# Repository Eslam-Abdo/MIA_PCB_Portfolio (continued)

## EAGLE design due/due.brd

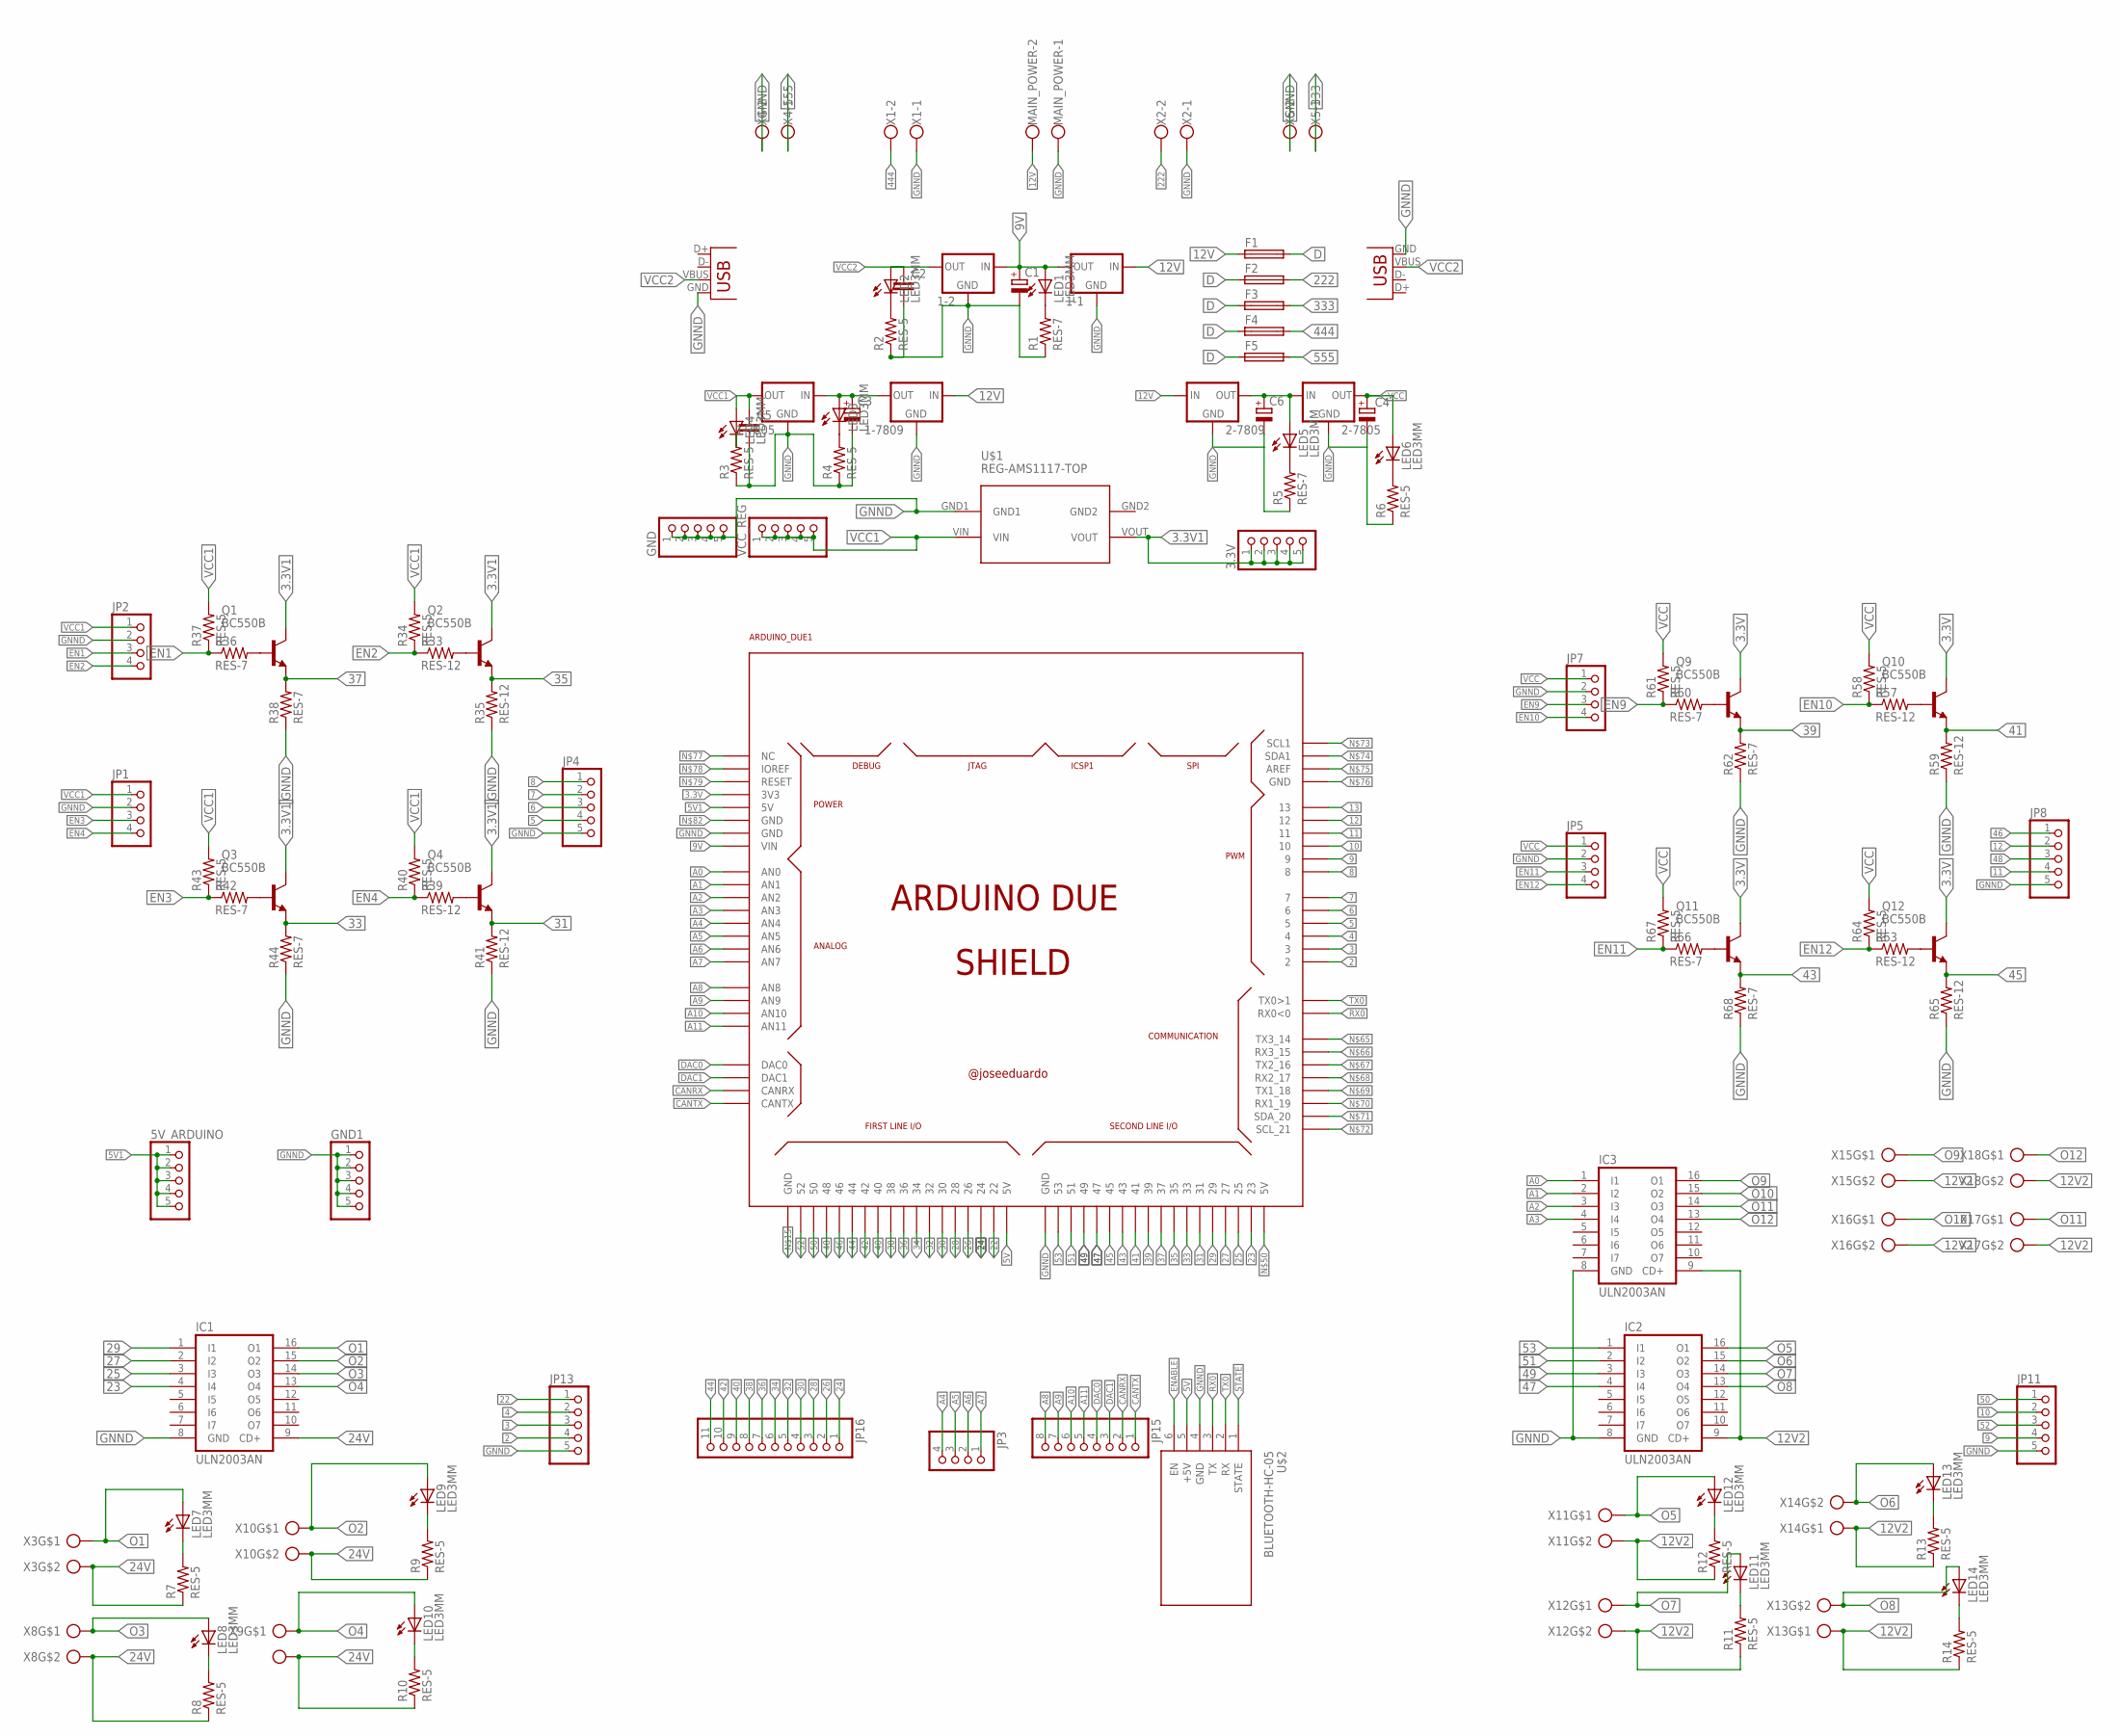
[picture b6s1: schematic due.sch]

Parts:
1-1, 1-2, 1-7805, 1-7809, 2-7805, 2-7809: 78XXS
3.3V, 5V_ARDUINO: PINHD-1X5; 1X05
ARDUINO_DUE1: ARDUINO_DUE_SHIELD
C1, C3, C4, C6: CAP_POL; E3,5-8
C2, C5: CAPACITOR; C025-025X050
F1, F2, F3, F4, F5: FUSE_HOLDER; SH22,5A
GND, GND1: PINHD-1X5; 1X05
IC1, IC2, IC3: ULN2003AN; DIL16
JP1, JP2, JP3, JP5, JP7: PINHD-1X4; 1X04
JP4, JP8, JP11, JP13: PINHD-1X5; 1X05
JP15: PINHD-1X8; 1X08
JP16: PINHD-1X11; 1X11
LED1, LED2, LED3, LED4, LED5, LED6, LED7, LED8, LED9, LED10, LED11, LED12, LED13, LED14: LED3MM
MAIN_POWER: ROSTA.POWER; W239-302
Q1, Q2, Q3, Q4, Q9, Q10, Q11, Q12: BC550B; TO92-EBC
R1, R5, R36, R38, R42, R44, R60, R62, R66, R68: RES-7; 0204/7
R2, R3, R4, R6, R7, R8, R9, R10, R11, R12, R13, R14, R34, R37, R40, R43, R58, R61, R64, R67: RES-5; 0204/5
R33, R35, R39, R41, R57, R59, R63, R65: RES-12; 0207/12
U$1: REG-AMS1117-TOP; REG-AMS1117_TOP
U$2: BLUETOOTH-HC-05; WIRELESS-BLUETOOTH-HC-05
VCC_REG: PINHD-1X5; 1X05
X1, X2, X4, X5: ROSTA.POWER; W239-302
X3, X8, X9, X10, X11, X12, X13, X14, X15, X16, X17, X18: CON_PTR_2; AK300/2
X6, X7: USB-A-H

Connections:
2: ARDUINO_DUE1.2, JP13.4
3: ARDUINO_DUE1.3, JP13.3
3.3V: ARDUINO_DUE1.3V3, Q9.C, Q10.C, Q11.C, Q12.C
3.3V1: 3.3V.1, 3.3V.2, 3.3V.3, 3.3V.4, 3.3V.5, Q1.C, Q2.C, Q3.C, Q4.C, U$1.VOUT
4: ARDUINO_DUE1.4, JP13.2
5: ARDUINO_DUE1.5, JP4.4
5V: ARDUINO_DUE1.5V0_1 (5V), U$2.5 (+5V)
5V1: 5V_ARDUINO.1, 5V_ARDUINO.2, 5V_ARDUINO.3, 5V_ARDUINO.4, 5V_ARDUINO.5, ARDUINO_DUE1.5V0 (5V)
6: ARDUINO_DUE1.6, JP4.3
7: ARDUINO_DUE1.7, JP4.2
8: ARDUINO_DUE1.8, JP4.1
9: ARDUINO_DUE1.9, JP11.4
9V: 1-1.OUT, 1-2.IN, ARDUINO_DUE1.VIN, C1.+, LED1.A
10: ARDUINO_DUE1.10, JP11.2
11: ARDUINO_DUE1.11, JP8.4
12: ARDUINO_DUE1.12, JP8.2
12V: 1-1.IN, 1-7809.IN, 2-7809.IN, F1.1, MAIN_POWER.2
12V2: IC2.9 (CD+), IC3.9 (CD+), R11.1, R12.1, R13.1, R14.1, X11.2, X12.2, X13.1, X14.1, X15.2, X16.2, X17.2, X18.2
13: ARDUINO_DUE1.13
22: ARDUINO_DUE1.22, JP13.1
23: ARDUINO_DUE1.23, IC1.4 (I4)
24: ARDUINO_DUE1.24, JP16.1
24V: IC1.9 (CD+), R7.1, R8.1, R9.1, R10.1, X3.2, X8.2, X9.2, X10.2
25: ARDUINO_DUE1.25, IC1.3 (I3)
26: ARDUINO_DUE1.26, JP16.2
27: ARDUINO_DUE1.27, IC1.2 (I2)
28: ARDUINO_DUE1.28, JP16.3
29: ARDUINO_DUE1.29, IC1.1 (I1)
30: ARDUINO_DUE1.30, JP16.4
31: ARDUINO_DUE1.31, Q4.E, R41.2
32: ARDUINO_DUE1.32, JP16.5
33: ARDUINO_DUE1.33, Q3.E, R44.2
34: ARDUINO_DUE1.34, JP16.6
35: ARDUINO_DUE1.35, Q2.E, R35.2
36: ARDUINO_DUE1.36, JP16.7
37: ARDUINO_DUE1.37, Q1.E, R38.2
38: ARDUINO_DUE1.38, JP16.8
39: ARDUINO_DUE1.39, Q9.E, R62.2
40: ARDUINO_DUE1.40, JP16.9
41: ARDUINO_DUE1.41, Q10.E, R59.2
42: ARDUINO_DUE1.42, JP16.10
43: ARDUINO_DUE1.43, Q11.E, R68.2
44: ARDUINO_DUE1.44, JP16.11
45: ARDUINO_DUE1.45, Q12.E, R65.2
46: ARDUINO_DUE1.46, JP8.1
47: ARDUINO_DUE1.47, IC2.4 (I4)
48: ARDUINO_DUE1.48, JP8.3
49: ARDUINO_DUE1.49, IC2.3 (I3)
50: ARDUINO_DUE1.50, JP11.1
51: ARDUINO_DUE1.51, IC2.2 (I2)
52: ARDUINO_DUE1.52, JP11.3
53: ARDUINO_DUE1.53, IC2.1 (I1)
222: F2.2, X2.2
333: F3.2, X5.1
444: F4.2, X1.2
555: F5.2, X4.1
A0: ARDUINO_DUE1.A0 (AN0), IC3.1 (I1)
A1: ARDUINO_DUE1.A1 (AN1), IC3.2 (I2)
A2: ARDUINO_DUE1.A2 (AN2), IC3.3 (I3)
A3: ARDUINO_DUE1.A3 (AN3), IC3.4 (I4)
A4: ARDUINO_DUE1.A4 (AN4), JP3.4
A5: ARDUINO_DUE1.A5 (AN5), JP3.3
A6: ARDUINO_DUE1.A6 (AN6), JP3.2
A7: ARDUINO_DUE1.A7 (AN7), JP3.1
A8: ARDUINO_DUE1.A8 (AN8), JP15.8
A9: ARDUINO_DUE1.A9 (AN9), JP15.7
A10: ARDUINO_DUE1.A10 (AN10), JP15.6
A11: ARDUINO_DUE1.A11 (AN11), JP15.5
CANRX: ARDUINO_DUE1.CANRX, JP15.2
CANTX: ARDUINO_DUE1.CANTX, JP15.1
D: F1.2, F2.1, F3.1, F4.1, F5.1
DAC0: ARDUINO_DUE1.DAC0, JP15.4
DAC1: ARDUINO_DUE1.DAC1, JP15.3
EN1: JP2.3, R36.1, R37.1
EN2: JP2.4, R33.1, R34.1
EN3: JP1.3, R42.1, R43.1
EN4: JP1.4, R39.1, R40.1
EN9: JP7.3, R60.1, R61.1
EN10: JP7.4, R57.1, R58.1
EN11: JP5.3, R66.1, R67.1
EN12: JP5.4, R63.1, R64.1
ENABLE: U$2.6 (EN)
GNND: 1-1.GND, 1-2.GND, 1-7805.GND, 1-7809.GND, 2-7805.GND, 2-7809.GND, ARDUINO_DUE1.GND_1 (GND), ARDUINO_DUE1.GND_3 (GND), C1.-, C2.2, C3.-, C4.-, C5.2, C6.-, GND.1, GND.2, GND.3, GND.4, GND.5, GND1.1, GND1.2, GND1.3, GND1.4, GND1.5, IC1.8 (GND), IC2.8 (GND), IC3.8 (GND), JP1.2, JP2.2, JP4.5, JP5.2, JP7.2, JP8.5, JP11.5, JP13.5, MAIN_POWER.1, R1.1, R2.1, R3.1, R4.1, R5.1, R6.1, R35.1, R38.1, R41.1, R44.1, R59.1, R62.1, R65.1, R68.1, U$1.GND1, U$2.4 (GND), X1.1, X2.1, X4.2, X5.2, X6.GND, X7.GND
unnamed: LED12.K (C), R12.2
unnamed: LED1.K (C), R1.2
unnamed: C2.1, LED2.A
unnamed: LED4.K (C), R3.2
unnamed: LED3.K (C), R4.2
unnamed: 2-7805.IN, 2-7809.OUT, C6.+, LED5.A
unnamed: LED2.K (C), R2.2
unnamed: LED5.K (C), R5.2
unnamed: LED6.K (C), R6.2
unnamed: LED11.K (C), R11.2
unnamed: LED13.K (C), R13.2
unnamed: LED14.K (C), R14.2
unnamed: LED10.K (C), R10.2
unnamed: LED9.K (C), R9.2
unnamed: 1-7805.IN, 1-7809.OUT, C3.+, LED3.A
unnamed: LED8.K (C), R8.2
unnamed: LED7.K (C), R7.2
unnamed: Q2.B, R33.2
unnamed: Q1.B, R36.2
unnamed: Q4.B, R39.2
unnamed: Q3.B, R42.2
unnamed: Q10.B, R57.2
unnamed: Q9.B, R60.2
unnamed: Q12.B, R63.2
unnamed: Q11.B, R66.2
O1: IC1.16 (O1), LED7.A, X3.1
O2: IC1.15 (O2), LED9.A, X10.1
O3: IC1.14 (O3), LED8.A, X8.1
O4: IC1.13 (O4), LED10.A, X9.1
O5: IC2.16 (O1), LED12.A, X11.1
O6: IC2.15 (O2), LED13.A, X14.2
O7: IC2.14 (O3), LED11.A, X12.1
O8: IC2.13 (O4), LED14.A, X13.2
O9: IC3.16 (O1), X15.1
O10: IC3.15 (O2), X16.1
O11: IC3.14 (O3), X17.1
O12: IC3.13 (O4), X18.1
RX0: ARDUINO_DUE1.0 (RX0<0), U$2.3 (TX)
STATE: U$2.1 (STATE)
TX0: ARDUINO_DUE1.1 (TX0>1), U$2.2 (RX)
VCC: 2-7805.OUT, C4.+, JP5.1, JP7.1, LED6.A, R58.2, R61.2, R64.2, R67.2
VCC1: 1-7805.OUT, C5.1, JP1.1, JP2.1, LED4.A, R34.2, R37.2, R40.2, R43.2, U$1.VIN, VCC_REG.1, VCC_REG.2, VCC_REG.3, VCC_REG.4, VCC_REG.5
VCC2: 1-2.OUT, X6.VBUS, X7.VBUS

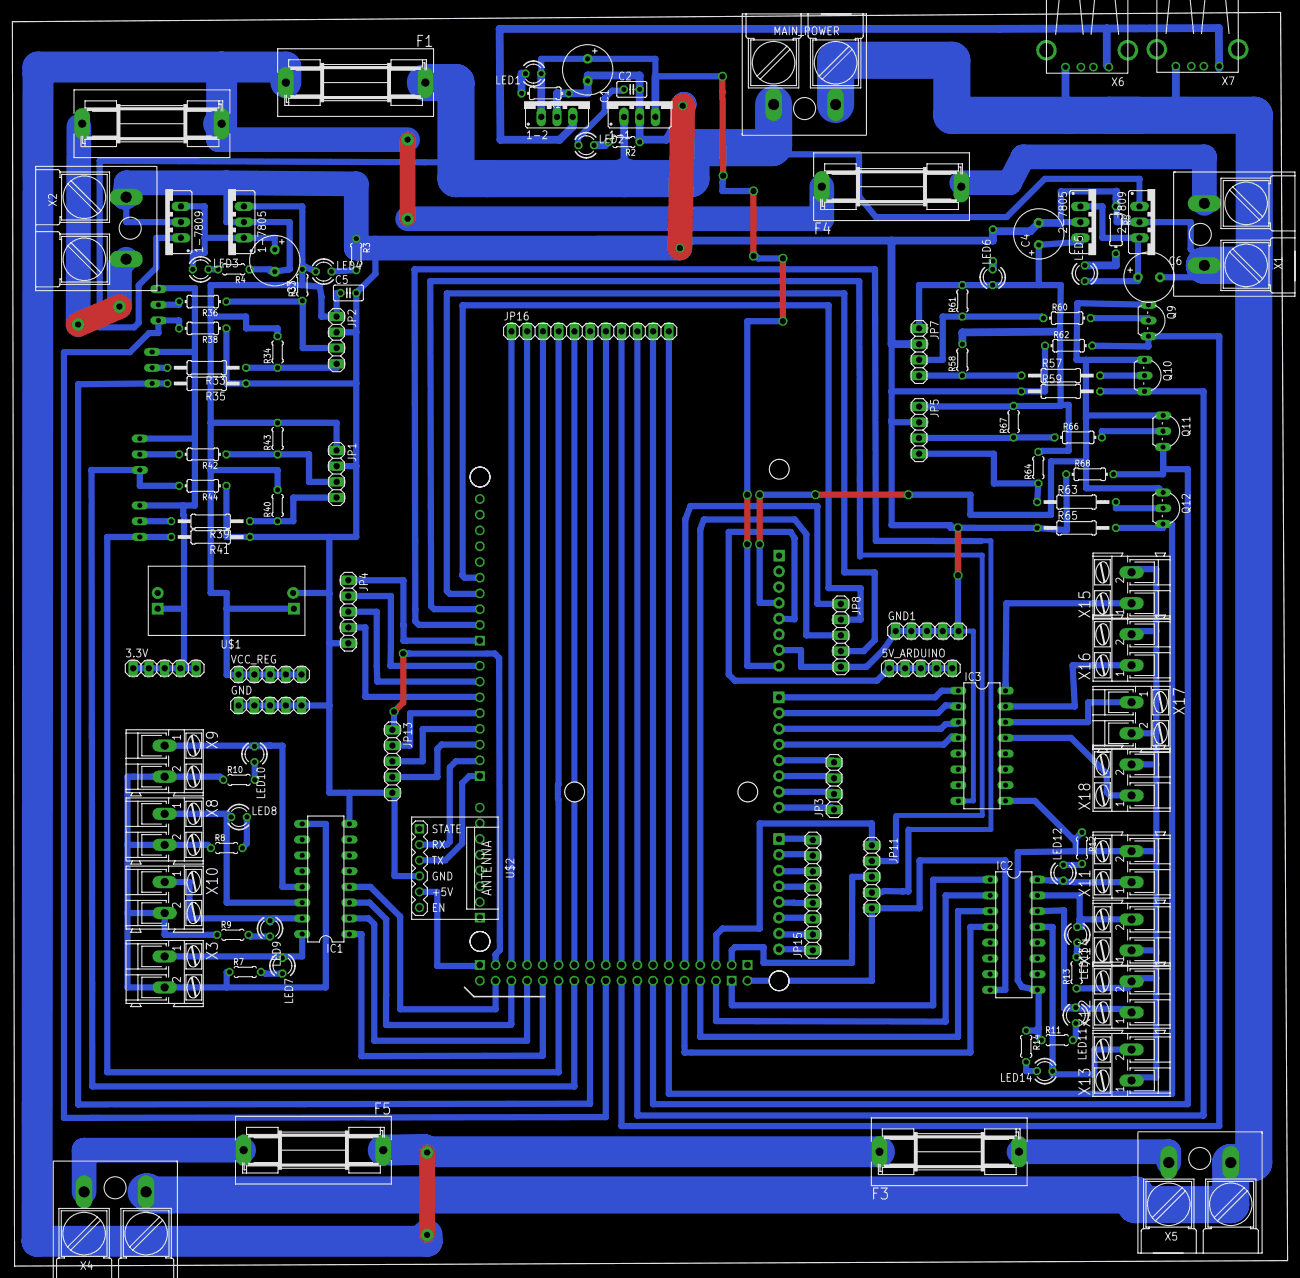
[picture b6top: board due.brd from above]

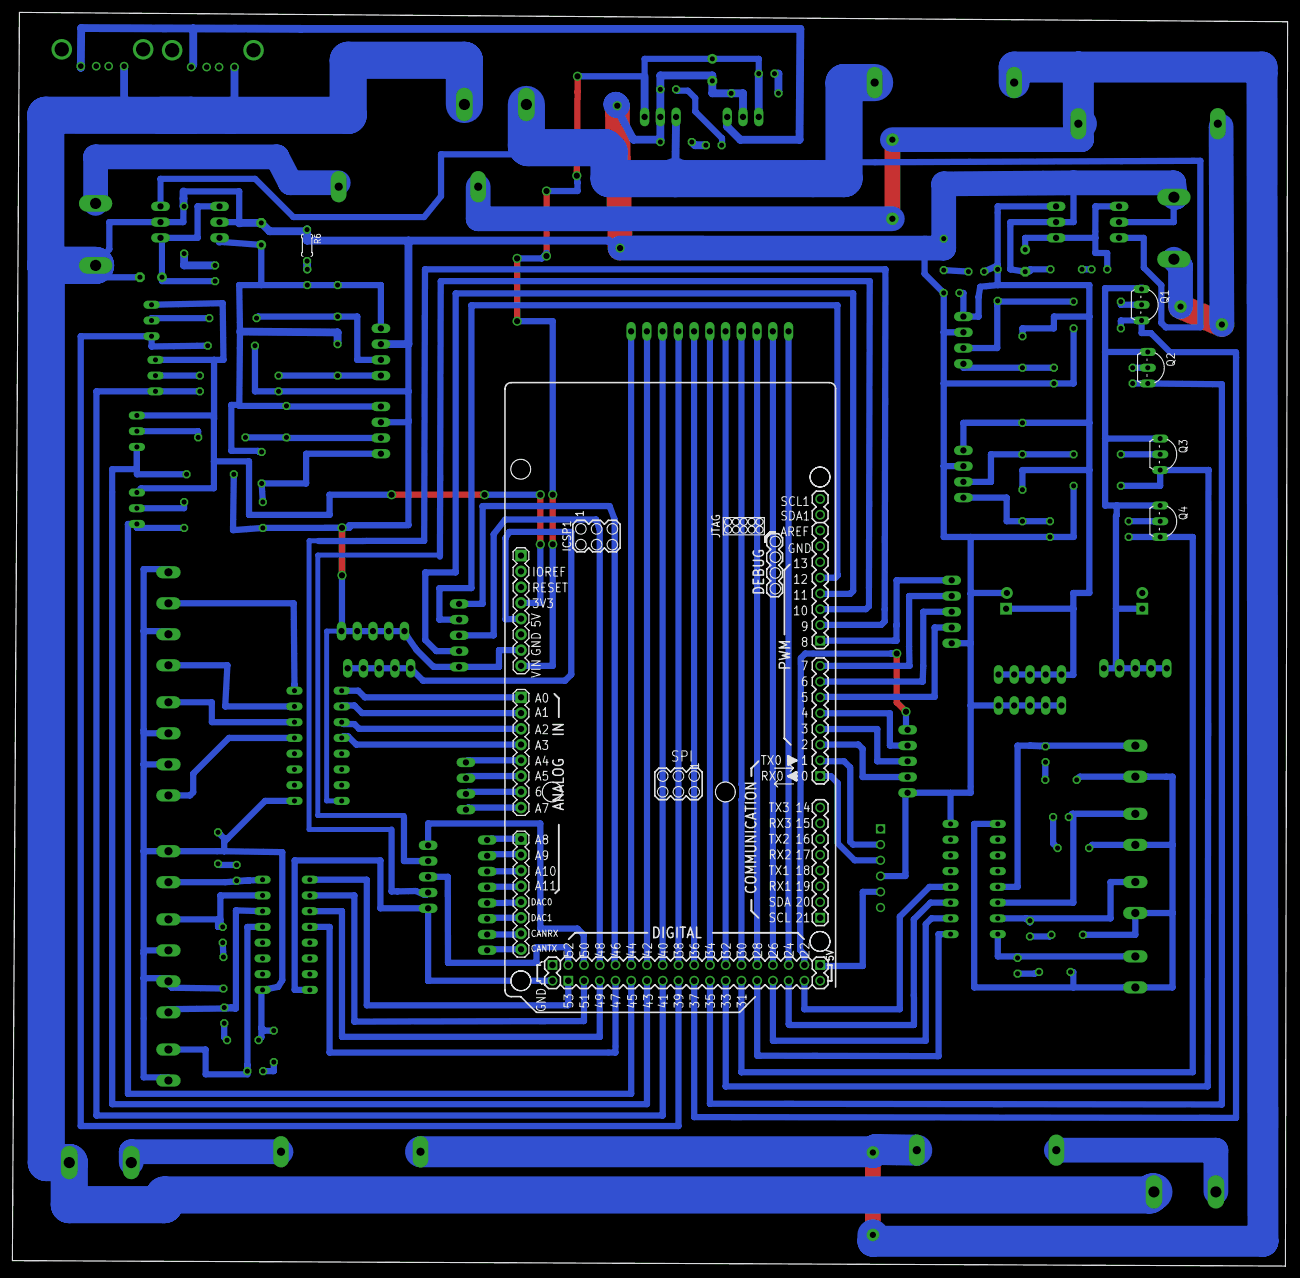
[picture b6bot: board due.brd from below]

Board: 2 copper layers, 205.7 x 202.3 mm, 118 parts (6 on the bottom side), 123 nets.

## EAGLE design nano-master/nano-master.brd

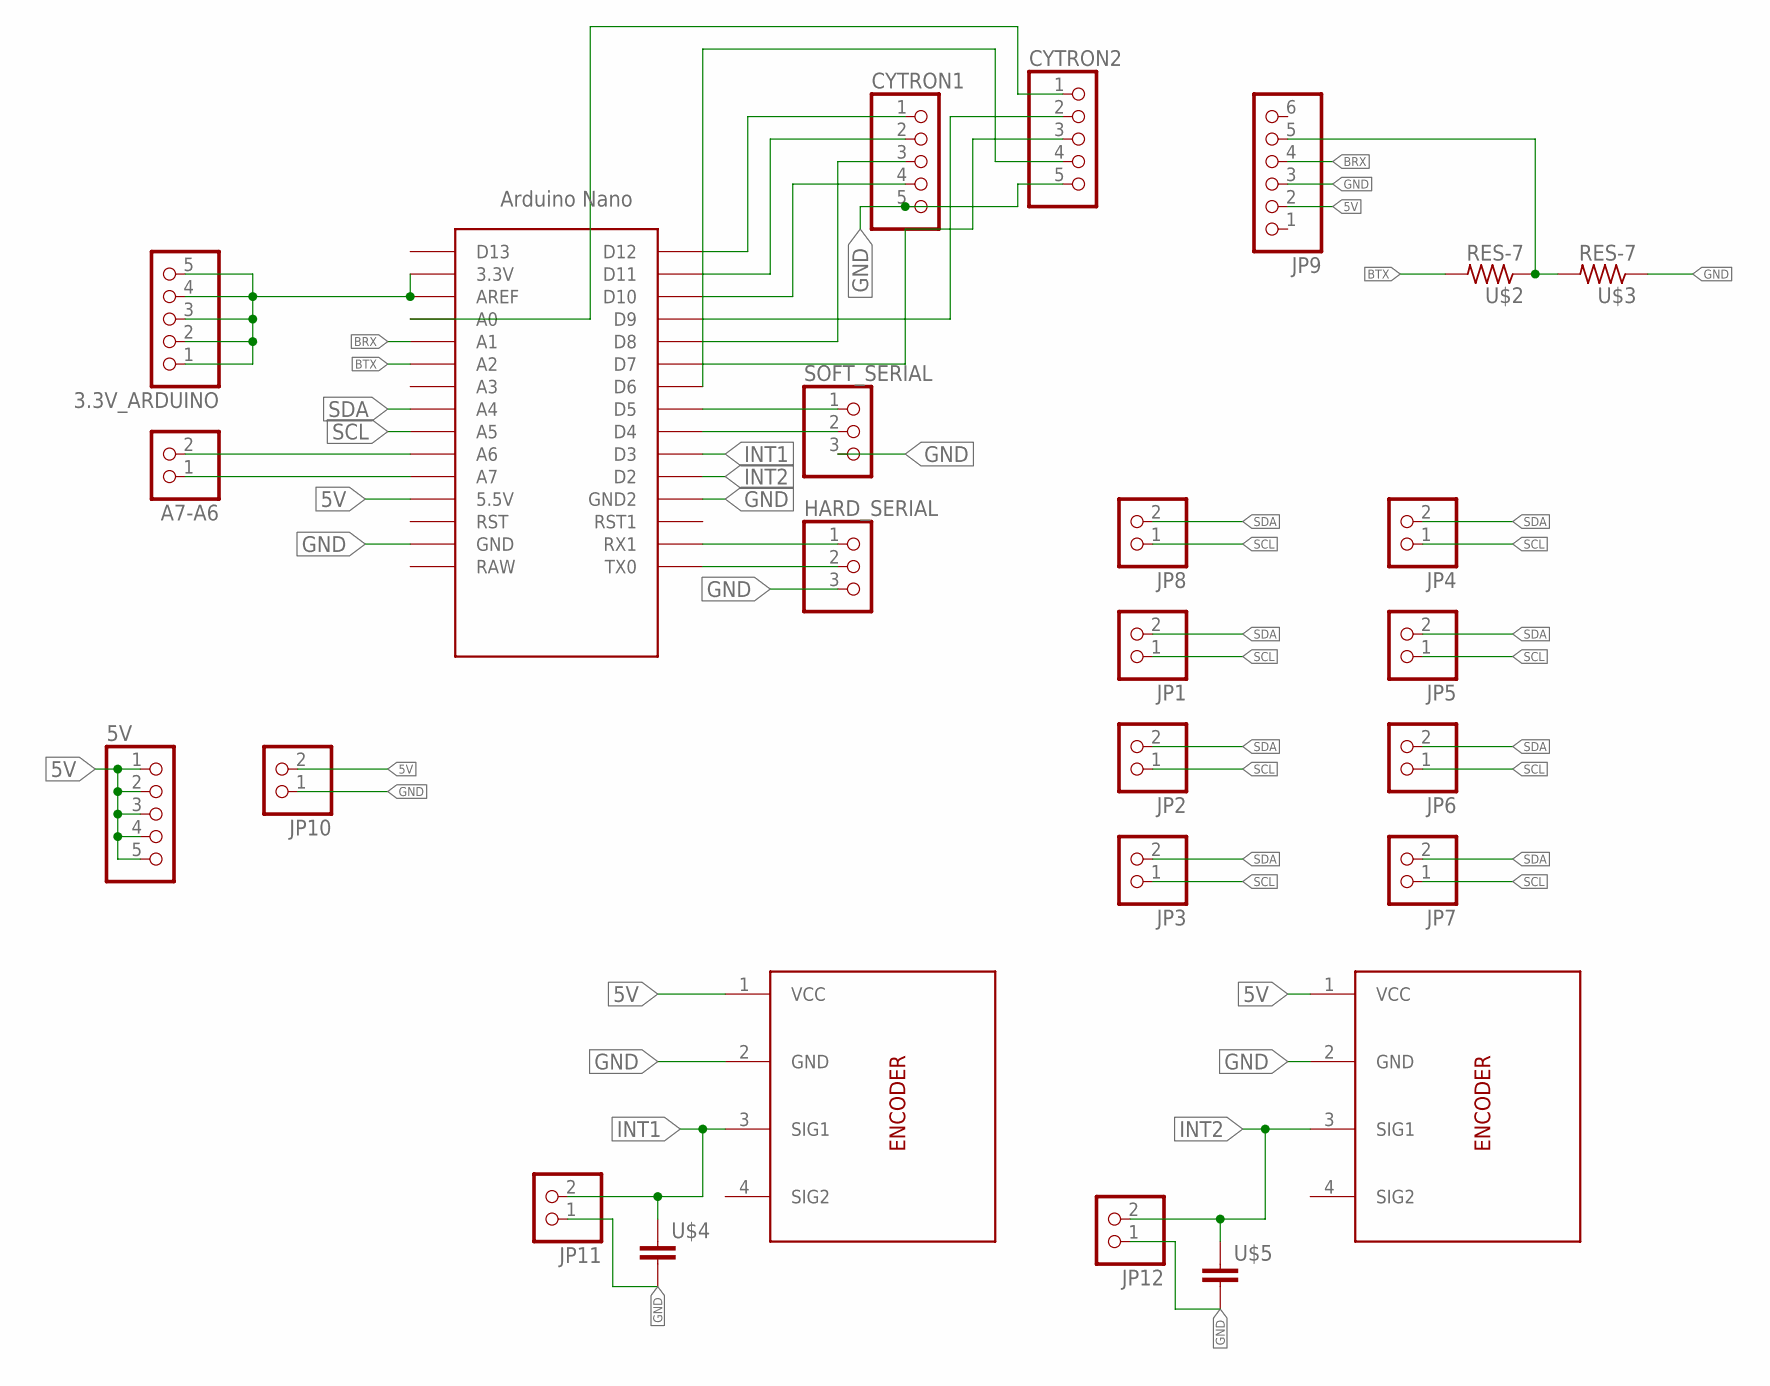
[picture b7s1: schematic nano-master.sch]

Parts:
3.3V_ARDUINO, 5V: PINHD-1X5; 1X05
A7-A6: PINHD-1X2; 1X02
CYTRON1, CYTRON2: PINHD-1X5; 1X05
ENCODER1, ENCODER2: ENCODER; 1X04_DATA
HARD_SERIAL: PINHD-1X3; 1X03
JP1, JP2, JP3, JP4, JP5, JP6, JP7, JP8, JP10, JP11, JP12: PINHD-1X2; 1X02
JP9: PINHD-1X6; 1X06
SOFT_SERIAL: PINHD-1X3; 1X03
U$1: ARDUINO_NANO; NANO
U$2, U$3: RES-7; 0204/7
U$4, U$5: CAPACITOR; C025-025X050

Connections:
5V: 5V.1, 5V.2, 5V.3, 5V.4, 5V.5, ENCODER1.1 (VCC), ENCODER2.1 (VCC), JP9.2, JP10.2, U$1.5V (5.5V)
BRX: JP9.4, U$1.A1
BTX: U$1.A2, U$2.2
GND: CYTRON1.5, CYTRON2.5, ENCODER1.2 (GND), ENCODER2.2 (GND), HARD_SERIAL.3, JP9.3, JP10.1, JP11.1, JP12.1, SOFT_SERIAL.3, U$1.GND, U$1.GND1 (GND2), U$3.1, U$4.2, U$5.2
INT1: ENCODER2.3 (SIG1), JP11.2, U$1.D3, U$4.1
INT2: ENCODER1.3 (SIG1), JP12.2, U$1.D2, U$5.1
unnamed: SOFT_SERIAL.1, U$1.D5
unnamed: SOFT_SERIAL.2, U$1.D4
unnamed: HARD_SERIAL.1, U$1.RX1
unnamed: HARD_SERIAL.2, U$1.TX0
unnamed: CYTRON1.1, U$1.D12
unnamed: CYTRON1.2, U$1.D11
unnamed: CYTRON1.4, U$1.D10
unnamed: CYTRON2.2, U$1.D9
unnamed: CYTRON1.3, U$1.D8
unnamed: CYTRON2.3, U$1.D7
unnamed: CYTRON2.4, U$1.D6
unnamed: CYTRON2.1, U$1.A0
unnamed: JP9.5, U$2.1, U$3.2
unnamed: A7-A6.1, U$1.A7
unnamed: A7-A6.2, U$1.A6
unnamed: 3.3V_ARDUINO.1, 3.3V_ARDUINO.2, 3.3V_ARDUINO.3, 3.3V_ARDUINO.4, 3.3V_ARDUINO.5, U$1.3.3V, U$1.AREF
SCL: JP1.1, JP2.1, JP3.1, JP4.1, JP5.1, JP6.1, JP7.1, JP8.1, U$1.A5
SDA: JP1.2, JP2.2, JP3.2, JP4.2, JP5.2, JP6.2, JP7.2, JP8.2, U$1.A4

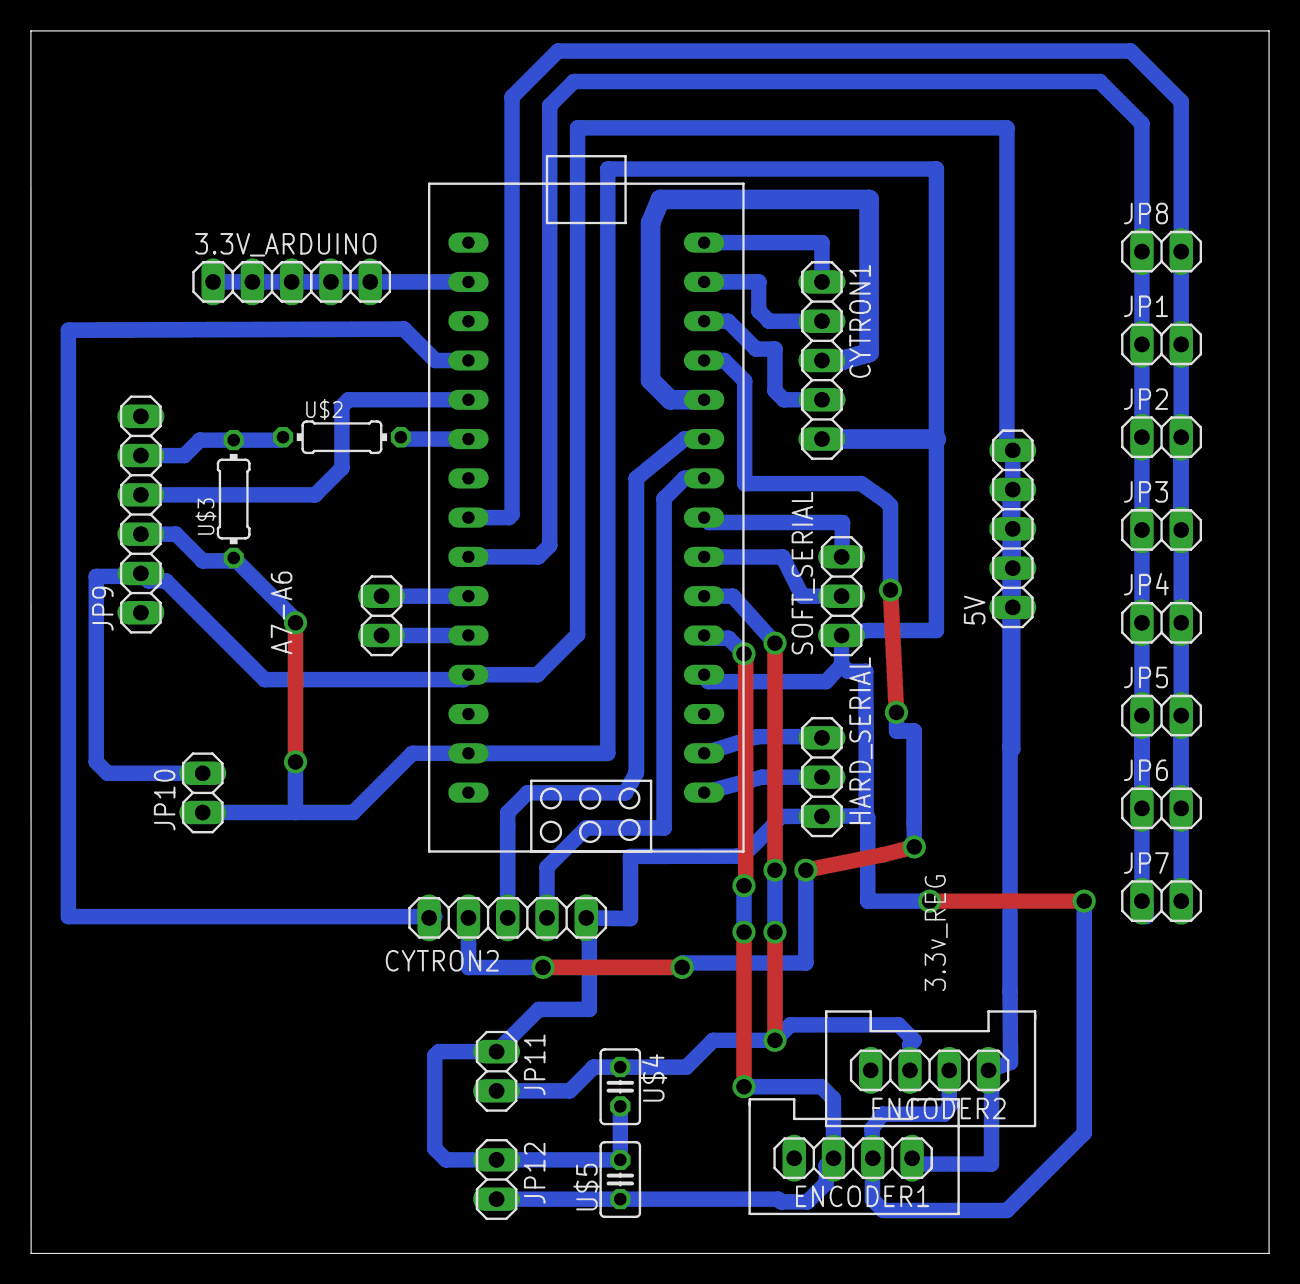
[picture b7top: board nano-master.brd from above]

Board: 2 copper layers, 80.1 x 79.1 mm, 26 parts (0 on the bottom side), 24 nets.

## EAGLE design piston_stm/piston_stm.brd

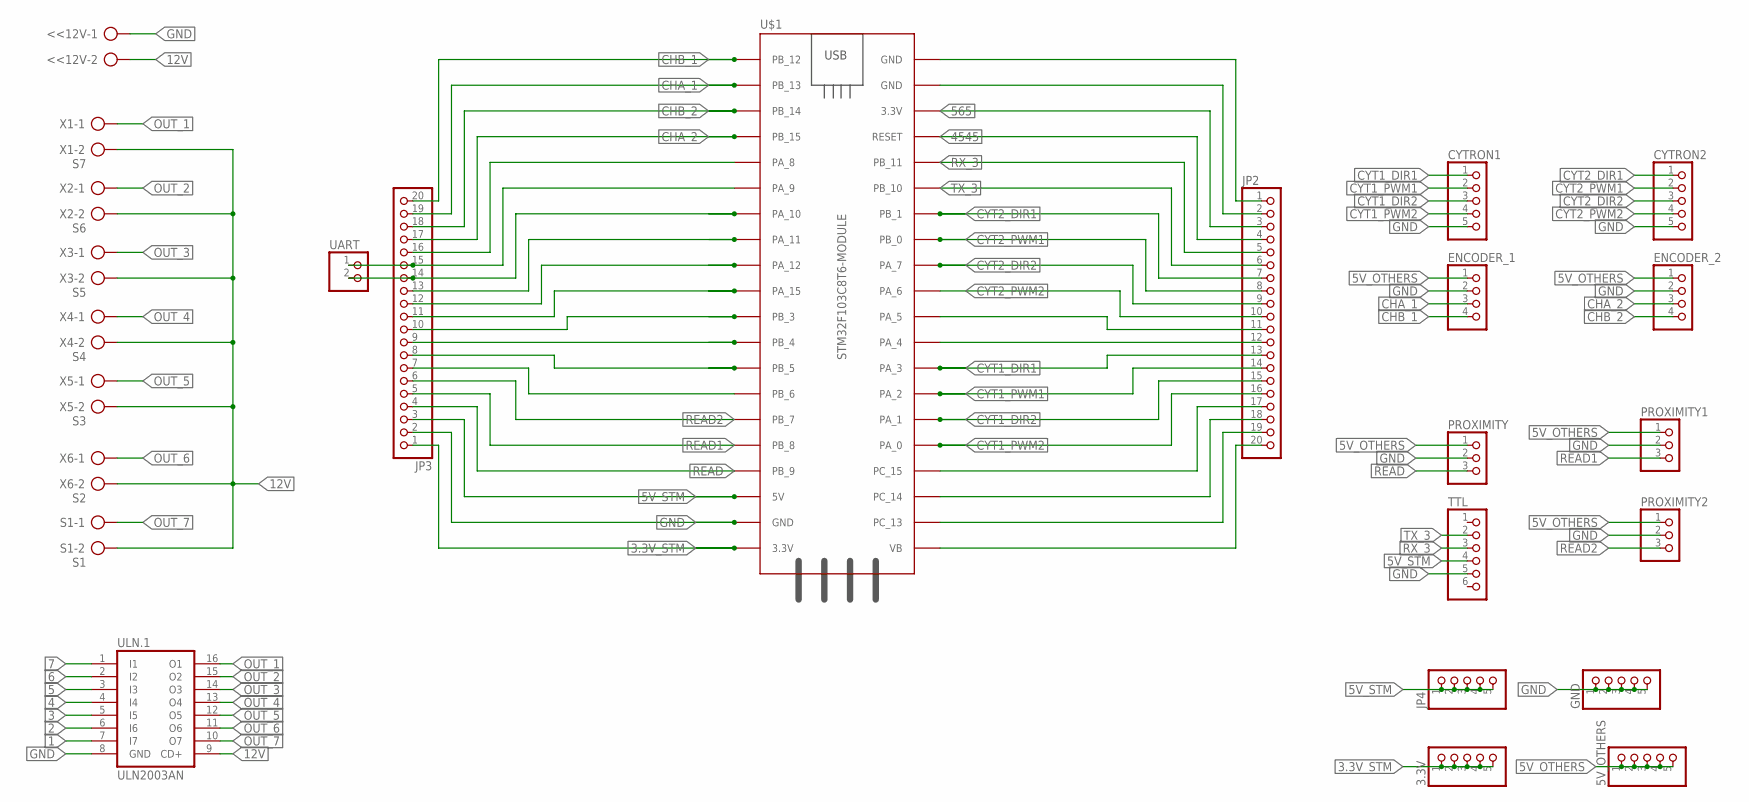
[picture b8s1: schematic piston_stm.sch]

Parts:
3.3V, 5V_OTHERS: PINHD-1X5; 1X05
<<12V: AK300/2
CYTRON1, CYTRON2: PINHD-5_DATA; 1X05_DATA
ENCODER_1, ENCODER_2: PINHD-4_DATA; 1X04_DATA
GND: PINHD-1X5; 1X05
JP2, JP3: PINHD-1X20; 1X20
JP4: PINHD-1X5; 1X05
PROXIMITY, PROXIMITY1, PROXIMITY2: PINHD-3_DATA; 1X03_DATA
S1: S1; AK300/2
TTL: PINHD-6_DATA; 1X06_DATA
U$1: STM32F103C8T6-MODULE
UART: PINHD-2_DATA; 1X02_DATA
ULN.1: ULN2003AN; DIL16
X1: S7; AK300/2
X2: S6; AK300/2
X3: S5; AK300/2
X4: S4; AK300/2
X5: S3; AK300/2
X6: S2; AK300/2

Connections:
0: JP3.7, U$1.PB_6
1: JP3.13, U$1.PA_11, ULN.1.7 (I7)
2: JP3.12, U$1.PA_12, ULN.1.6 (I6)
3: JP3.11, U$1.PA_15, ULN.1.5 (I5)
3.3V_STM: 3.3V.1, 3.3V.2, 3.3V.3, 3.3V.4, 3.3V.5, JP3.1, U$1.3.3V_1 (3.3V)
4: JP3.10, U$1.PB_3, ULN.1.4 (I4)
5: JP3.9, U$1.PB_4, ULN.1.3 (I3)
5V_OTHERS: 5V_OTHERS.1, 5V_OTHERS.2, 5V_OTHERS.3, 5V_OTHERS.4, 5V_OTHERS.5, ENCODER_1.1, ENCODER_2.1, PROXIMITY.1, PROXIMITY1.1, PROXIMITY2.1
5V_STM: JP3.3, JP4.1, JP4.2, JP4.3, JP4.4, JP4.5, TTL.4, U$1.5V
6: JP3.8, U$1.PB_5, ULN.1.2 (I2)
7: JP2.12, U$1.PA_4, ULN.1.1 (I1)
12V: <<12V.2, S1.2, ULN.1.9 (CD+), X1.2, X2.2, X3.2, X4.2, X5.2, X6.2
565: JP2.3, U$1.3.3V_2 (3.3V)
4545: JP2.4, U$1.RESET
54454: JP3.14, U$1.PA_10, UART.2
CHA_1: ENCODER_1.3, JP3.19, U$1.PB_13
CHA_2: ENCODER_2.3, JP3.17, U$1.PB_15
CHB_1: ENCODER_1.4, JP3.20, U$1.PB_12
CHB_2: ENCODER_2.4, JP3.18, U$1.PB_14
CYT1_DIR1: CYTRON1.1, JP2.13, U$1.PA_3
CYT1_DIR2: CYTRON1.3, JP2.15, U$1.PA_1
CYT1_PWM1: CYTRON1.2, JP2.14, U$1.PA_2
CYT1_PWM2: CYTRON1.4, JP2.16, U$1.PA_0
CYT2_DIR1: CYTRON2.1, JP2.7, U$1.PB_1
CYT2_DIR2: CYTRON2.3, JP2.9, U$1.PA_7
CYT2_PWM1: CYTRON2.2, JP2.8, U$1.PB_0
CYT2_PWM2: CYTRON2.4, JP2.10, U$1.PA_6
GND: <<12V.1, CYTRON1.5, CYTRON2.5, ENCODER_1.2, ENCODER_2.2, GND.1, GND.2, GND.3, GND.4, GND.5, JP2.1, JP2.2, JP3.2, PROXIMITY.2, PROXIMITY1.2, PROXIMITY2.2, TTL.5, U$1.GND_1 (GND), U$1.GND_2 (GND), U$1.GND_3 (GND), ULN.1.8 (GND)
unnamed: JP2.11, U$1.PA_5
unnamed: JP2.20, U$1.VB
unnamed: JP2.19, U$1.PC_13
unnamed: JP2.18, U$1.PC_14
unnamed: JP2.17, U$1.PC_15
unnamed: JP3.16, U$1.PA_8
unnamed: JP3.15, U$1.PA_9, UART.1
OUT_1: ULN.1.16 (O1), X1.1
OUT_2: ULN.1.15 (O2), X2.1
OUT_3: ULN.1.14 (O3), X3.1
OUT_4: ULN.1.13 (O4), X4.1
OUT_5: ULN.1.12 (O5), X5.1
OUT_6: ULN.1.11 (O6), X6.1
OUT_7: S1.1, ULN.1.10 (O7)
READ: JP3.4, PROXIMITY.3, U$1.PB_9
READ1: JP3.5, PROXIMITY1.3, U$1.PB_8
READ2: JP3.6, PROXIMITY2.3, U$1.PB_7
RX_3: JP2.5, TTL.3, U$1.PB_11
TX_3: JP2.6, TTL.2, U$1.PB_10

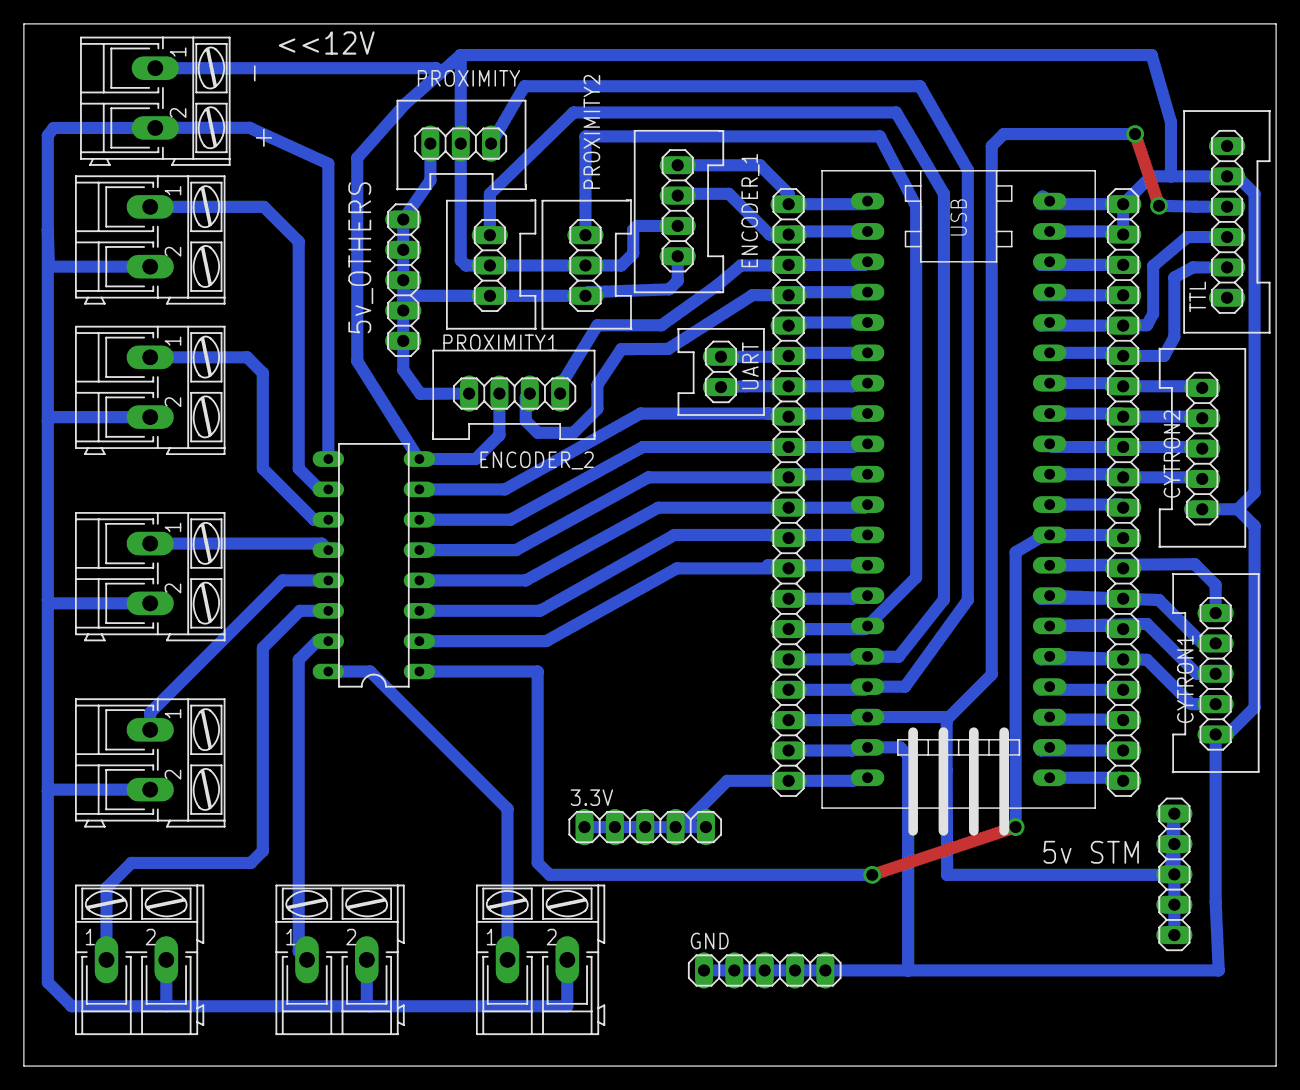
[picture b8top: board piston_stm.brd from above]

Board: 2 copper layers, 104.8 x 87.2 mm, 25 parts (0 on the bottom side), 47 nets.
